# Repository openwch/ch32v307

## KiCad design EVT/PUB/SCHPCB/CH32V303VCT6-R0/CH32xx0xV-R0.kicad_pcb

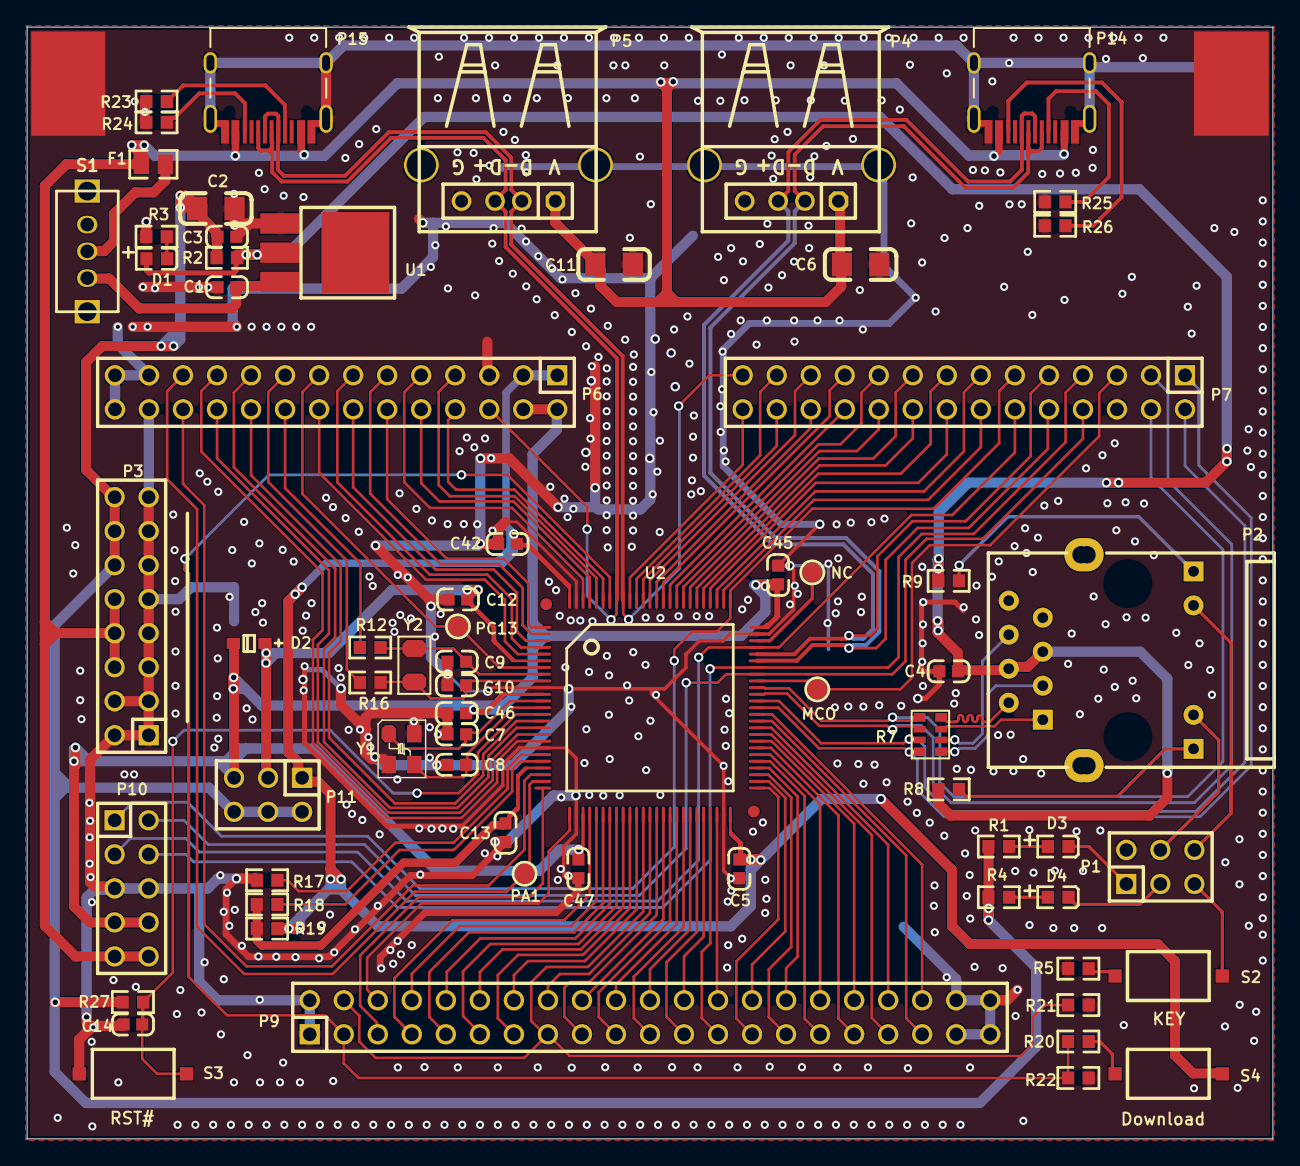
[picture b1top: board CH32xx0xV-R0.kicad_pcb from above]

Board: 2 copper layers, 93.0 x 83.0 mm, 68 parts (0 on the bottom side), 119 nets.

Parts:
C1, C3, C5, C12, C13, C14, C42, C45, C46, C47: 0.1uF; 0603_C
C2, C6, C11: 10uF; 3216_C
C4: 1uF; 0603_C
C7, C8: 22pF; 0603_C
C9, C10: 12pF; 0603_C
D1, D4: RED; 0603+
D2: B0520WS; SOD-323
D3: BLUE; 0603+
F1: 500mA; 0805
MCO: Testpoint; TESTPOINT1
NC: Testpoint; TESTPOINT1
P1: IO; IDC6-2.54mm
P2: HR911105A
P3: HEADER 8x2; IDC16-2.54mm
P4: USBFS; USBAF
P5: USBHS; USBAF
P6, P7: HEADER 14x2; IDC28-2.54MM
P9: HEADER 21x2; IDC42-2.54MM
P10: LINK; IDC10-2.54mm
P11: HEADER 3x2; IDC6-2.54mm
P14: USBFS; TYPE-C-Receptacle-2.0
P15: USBHS; TYPE-C-Receptacle-2.0
PA1: Testpoint; TESTPOINT1
PC13: Testpoint; TESTPOINT1
R1, R3, R4, R8, R9, R20: 1K; 0603
R2, R17, R18, R19: 0R; 0603
R5, R21, R22, R27: 10K; 0603
R7: 0Ω; RCA-8P4R-0603
R12, R16: NC(0R); 0603
R23: NC(5.1K); 0603
R24, R25, R26: 5.1K; 0603
S1: SW SPDT; KEY2
S2: KEY; SMD_6.1x3.65x2.5mm-KEY
S3: RST#; SMD_6.1x3.65x2.5mm-KEY
S4: Download; SMD_6.1x3.65x2.5mm-KEY
U1: 1117-3.3V; SOT-223
U2: CH32F207V; LQFP100
Y1: 8MHz; XT3225
Y2: 32768Hz; FC-135

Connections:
3V3: C2.1, C3.1, P3.12, P3.14, P3.16, P11.2, P11.4, P11.6, R1.1, R2.1, R4.1, R27.2
3V3S: C4.2, D1.1, P2.4, P2.5, R2.2, R8.1, R9.1, U1.2
5V: C6.1, C11.1, F1.1, P3.6, P3.8, P3.10, P4.1, P5.1, P10.9, P10.10, P14.A4, P14.B4, P15.A4, P15.B4
BOOT0: P9.3, R20.1, R22.1, U2.94
BOOT1: P9.4, P9.15, R21.1, U2.37
ELED1: P1.4, P2.10
ELED2: P1.6, P2.11
ERXN: P7.2, R7.3, U2.64
ERXN1: P2.6, R7.6
ERXP: P7.1, R7.4, U2.63
ERXP1: P2.3, R7.5
ETXN: P7.4, R7.1, U2.66
ETXN1: P2.2, R7.8
ETXP: P7.3, R7.2, U2.65
ETXP1: P2.1, R7.7
GND: C1.2, C2.2, C3.2, C4.1, C5.2, C6.2, C7.1, C8.1, C9.1, C10.1, C11.2, C12.1, C13.2, C14.1, C42.1, C45.2, C46.2, C47.1, P1.2, P2.8, P3.1, P3.2, P3.3, P3.4, P3.5, P3.7, P3.9, P3.11, P3.13, P3.15, P4.0, P4.4, P5.0, P5.4, P6.5, P6.25, P6.26, P6.27, P6.28, P7.6, P9.1, P9.2, P9.39, P9.40, P9.41, P9.42, P10.5, P10.6, P14.0, P14.A1, P14.B1, P15.0, P15.A1, P15.B1, R3.2, R5.1, R17.1, R21.2, R22.2, R23.2, R24.2, R25.2, R26.2, S3.1, U1.1, U2.10, U2.19, U2.27, U2.49, U2.74, U2.99, Y1.2, Y1.4
KEY: P1.5, S2.1
LED1: D3.2, P1.1
LED2: D4.2, P1.3
MCO: MCO.1, P7.5, U2.67
NC: NC.1, U2.73
NRST: C14.2, R27.1, S3.2, U2.14
NetC1_1: C1.1, S1.2, U1.3
NetD1_2: D1.2, R3.1
NetD3_1: D3.1, R1.2
NetD4_1: D4.1, R4.2
NetF1_2: F1.2, S1.1
NetP2_9: P2.9, R8.2
NetP2_12: P2.12, R9.2
NetP14_A5: P14.A5, R25.1
NetP14_B5: P14.B5, R26.1
NetP15_A5: P15.A5, R23.1
NetP15_B5: P15.B5, R24.1
NetR5_2: R5.2, S2.2
NetR20_2: R20.2, S4.2
PA0: P6.24, U2.23
PA1: P6.23, PA1.1, U2.24
PA2: P9.5, U2.25
PA3: P9.6, U2.26
PA4: P9.7, U2.29
PA5: P9.8, U2.30
PA6: P9.9, U2.31
PA7: P9.10, U2.32
PA9: P7.8, P10.2, U2.68
PA10: P7.7, P10.4, U2.69
PA11: P4.2, P7.10, P14.A7, P14.B7, U2.70
PA12: P4.3, P7.9, P14.A6, P14.B6, U2.71
PA13: P7.12, P10.3, U2.72
PA14: P7.11, P10.1, U2.76
PA15: P7.14, U2.77
PB0: P9.13, U2.35
PB1: P9.14, U2.36
PB3: P7.26, U2.89
PB4: P7.25, U2.90
PB5: P7.28, U2.91
PB6: P5.2, P7.27, P15.A7, P15.B7, U2.92
PB7: P5.3, P6.6, P15.A6, P15.B6, U2.93
PB8: P6.8, U2.95
PB9: P6.7, U2.96
PB10: P9.25, U2.47
PB11: P9.26, U2.48
PB12: P9.27, U2.51
PB13: P9.28, U2.52
PB14: P9.29, U2.53
PB15: P9.30, U2.54
PC0: P6.20, U2.15
PC1: P6.19, U2.16
PC2: P6.22, U2.17
PC3: P6.21, U2.18
PC4: P9.11, U2.33
PC5: P9.12, U2.34
PC10: P7.13, U2.78
PC11: P7.16, U2.79
PC12: P7.15, U2.80
PC13: P6.15, PC13.1, U2.7
PC14: P6.18, R12.1
PC15: P6.17, R16.1
PD0: P7.18, U2.81
PD1: P7.17, U2.82
PD2: P7.20, U2.83
PD3: P7.19, U2.84
PD4: P7.22, U2.85
PD5: P7.21, U2.86
PD6: P7.24, U2.87
PD7: P7.23, U2.88
PD8: P9.31, U2.55
PD9: P9.32, U2.56
PD10: P9.33, U2.57
PD11: P9.34, U2.58
PD12: P9.35, U2.59
PD13: P9.36, U2.60
PD14: P9.37, U2.61
PD15: P9.38, U2.62
PE0: P6.10, U2.97
PE1: P6.9, U2.98
PE2: P6.12, U2.1
PE3: P6.11, U2.2
PE4: P6.14, U2.3
PE5: P6.13, U2.4
PE6: P6.16, U2.5
PE7: P9.16, U2.38
PE8: P9.17, U2.39
PE9: P9.18, U2.40
PE10: P9.19, U2.41
PE11: P9.20, U2.42
PE12: P9.21, U2.43
PE13: P9.22, U2.44
PE14: P9.23, U2.45
PE15: P9.24, U2.46
VBAT: C12.2, D2.1, P11.3, U2.6
VDD: C45.1, C46.1, C47.2, D2.2, P6.2, P6.4, P10.7, P10.8, P11.5, U2.11, U2.28, U2.75
VDDA: C13.1, R18.1, R19.2, U2.22
VIO: C5.1, C42.2, P6.1, P6.3, P11.1, R19.1, S4.1, U2.50, U2.100
VREF+: R18.2, U2.21
VREF-: R17.2, U2.20
X32KI: C9.2, R12.2, U2.8, Y2.1
X32KO: C10.2, R16.2, U2.9, Y2.2
XI: C7.2, U2.12, Y1.1
XO: C8.2, U2.13, Y1.3
